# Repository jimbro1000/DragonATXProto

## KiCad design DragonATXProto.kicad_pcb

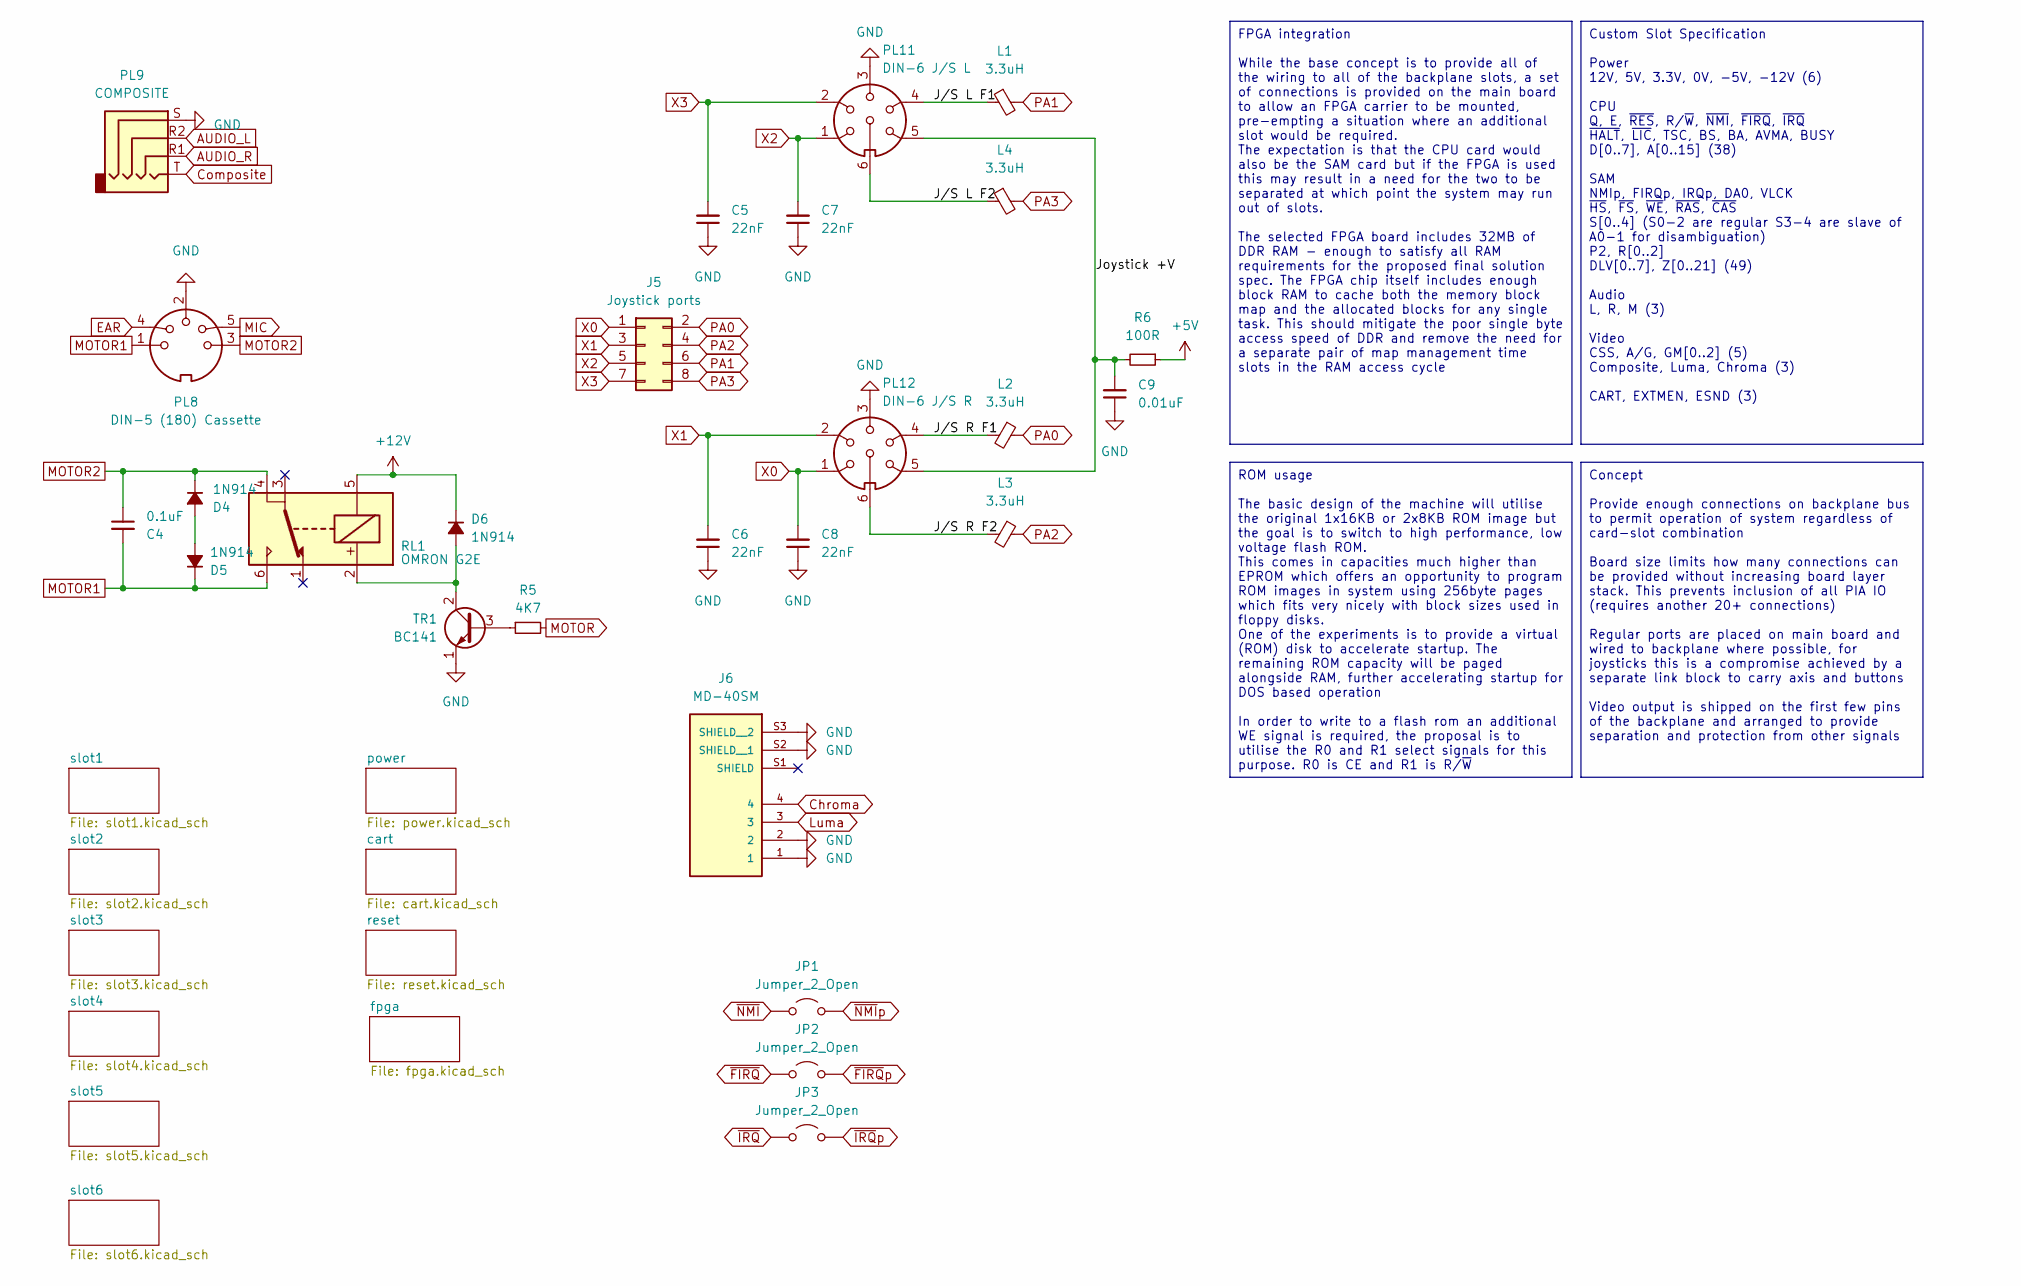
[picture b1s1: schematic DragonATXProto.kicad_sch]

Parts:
C4: 0.1uF; C_Disc_D4.3mm_W1.9mm_P5.00mm; DigiKey BC1101CT-ND
C5, C6, C7, C8: 22nF; C_Disc_D5.0mm_W2.5mm_P5.00mm; DigiKey BC2677CT-ND
C9: 0.01uF; C_Disc_D4.3mm_W1.9mm_P5.00mm; DigiKey BC2662CT-ND
D4, D5, D6: 1N914; D_DO-35_SOD27_P12.70mm_Horizontal; DigiKey 1N914FS-ND
J5: Joystick ports; PinHeader_2x04_P2.54mm_Vertical
J6: MD-40SM; CUI_MD-40SM; PARTREV 02/18/2022
JP1, JP2, JP3: Jumper_2_Open; SolderJumper-2_P1.3mm_Open_RoundedPad1.0x1.5mm
L1, L2, L3, L4: 3.3uH; L_Axial_L7.0mm_D3.3mm_P12.70mm_Horizontal_Fastron_MICC; DigiKey 495-5561-1-ND
PL8: DIN-5 (180) Cassette; DIN-5_DELTRON_671-0501_45deg_Horizontal
PL9: COMPOSITE; Jack_3.5mm_PJ320E_Horizontal
PL11: DIN-6 J/S L; DIN-6_DELTRON_671-0601_Horizontal
PL12: DIN-6 J/S R; DIN-6_DELTRON_671-0601_Horizontal
R5: 4K7; R_Axial_DIN0204_L3.6mm_D1.6mm_P2.54mm_Vertical; DigiKey CF14JT4K70CT-ND
R6: 100R; R_Axial_DIN0204_L3.6mm_D1.6mm_P2.54mm_Vertical; DigiKey CF14JT100RCT-ND
RL1: OMRON G2E; OMRON_G2E
TR1: BC141; TO-92

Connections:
+5V: R6.1; also elsewhere on the board
+12V: D6.1 (K), RL1.5; also elsewhere on the board
/Joystick +V: C9.2, PL11.5, PL12.5, R6.2
/J/S L F1: L1.1, PL11.4
/J/S L F2: L4.1, PL11.6
/J/S R F1: L2.2, PL12.4
/J/S R F2: L3.2, PL12.6
AUDIO_L: PL9.R2; also elsewhere on the board
AUDIO_R: PL9.R1; also elsewhere on the board
Chroma: J6.4; also elsewhere on the board
Composite: PL9.T; also elsewhere on the board
EAR: PL8.4; also elsewhere on the board
GND: C5.1, C6.1, C7.1, C8.1, C9.1, J6.1, J6.2, J6.S2 (SHIELD__1), J6.S3 (SHIELD__2), PL8.2, PL9.S, PL11.3, PL12.3, TR1.1 (E); also elsewhere on the board
Luma: J6.3; also elsewhere on the board
MIC: PL8.5; also elsewhere on the board
MOTOR: R5.2; also elsewhere on the board
MOTOR1: C4.2, D5.1 (K), PL8.1, RL1.6
MOTOR2: C4.1, D4.1 (K), PL8.3, RL1.4
unnamed: D4.2 (A), D5.2 (A)
unnamed: D6.2 (A), RL1.2, TR1.2 (C)
unnamed: R5.1, TR1.3 (B)
PA0: J5.2, L2.1
PA1: J5.6, L1.2
PA2: J5.4, L3.1
PA3: J5.8, L4.2
X0: C8.2, J5.1, PL12.1
X1: C6.2, J5.3, PL12.2
X2: C7.2, J5.5, PL11.1
X3: C5.2, J5.7, PL11.2
~FIRQ: JP2.1 (A); also elsewhere on the board
~FIRQp: JP2.2 (B); also elsewhere on the board
~IRQ: JP3.1 (A); also elsewhere on the board
~IRQp: JP3.2 (B); also elsewhere on the board
~NMI: JP1.1 (A); also elsewhere on the board
~NMIp: JP1.2 (B); also elsewhere on the board

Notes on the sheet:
ROM usage The basic design of the machine will utilise the original 1x16KB or 2x8KB ROM image but the goal is to switch to high performance, low voltage flash ROM. This comes in capacities much higher than EPROM which offers an opportunity to program ROM images in system using 256byte pages which f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
FPGA integration While the base concept is to provide all of the wiring to all of the backplane slots, a set of connections is provided on the main board to allow an FPGA carrier to be mounted, pre-empting a situation where an additional slot would be required. The expectation is that the CPU card 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
Custom Slot Specification Power 12V, 5V, 3.3V, 0V, -5V, -12V (6) CPU Q, E, ~{RES}, R/~{W}, ~{NMI}, ~{FIRQ}, ~{IRQ} ~{HALT}, ~{LIC}, TSC, BS, BA, AVMA, BUSY D[0..7], A[0..15] (38) SAM NMIp, FIRQp, IRQp, DA0, VLCK ~{HS}, ~{FS}, ~{WE}, ~{RAS}, ~{CAS} S[0..4] (S0-2 are regular S3-4 are slave of A0-1 fo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
Concept Provide enough connections on backplane bus to permit operation of system regardless of card-slot combination Board size limits how many connections can be provided without increasing board layer stack. This prevents inclusion of all PIA IO (requires another 20+ connections) Regular ports a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

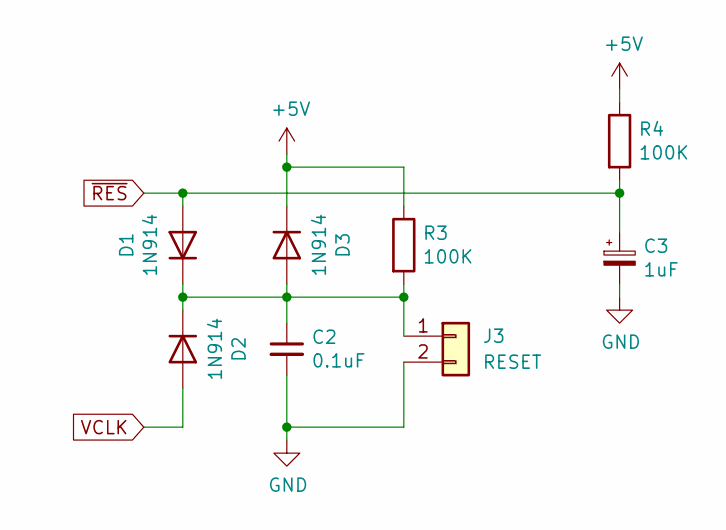
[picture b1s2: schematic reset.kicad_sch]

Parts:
C2: 0.1uF; C_Disc_D4.3mm_W1.9mm_P5.00mm; DigiKey 399-C0805C104K4RAC7800CT-ND
C3: 1uF; CP_Radial_D8.0mm_P5.00mm; DigiKey 732-8541-1-ND
D1, D2, D3: 1N914; D_DO-34_SOD68_P7.62mm_Horizontal; DigiKey 1N914FS-ND
J3: RESET; PinHeader_1x02_P2.54mm_Vertical
R3, R4: 100K; R_Axial_DIN0204_L3.6mm_D1.6mm_P2.54mm_Vertical; DigiKey 738-RNCF0805DTE100KCT-ND

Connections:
+5V: D3.1 (K), R3.1, R4.1; also elsewhere on the board
GND: C2.2, C3.2, J3.2; also elsewhere on the board
unnamed: C2.1, D1.1 (K), D2.1 (K), D3.2 (A), J3.1, R3.2
VCLK: D2.2 (A); also elsewhere on the board
~RES: C3.1, D1.2 (A), R4.2

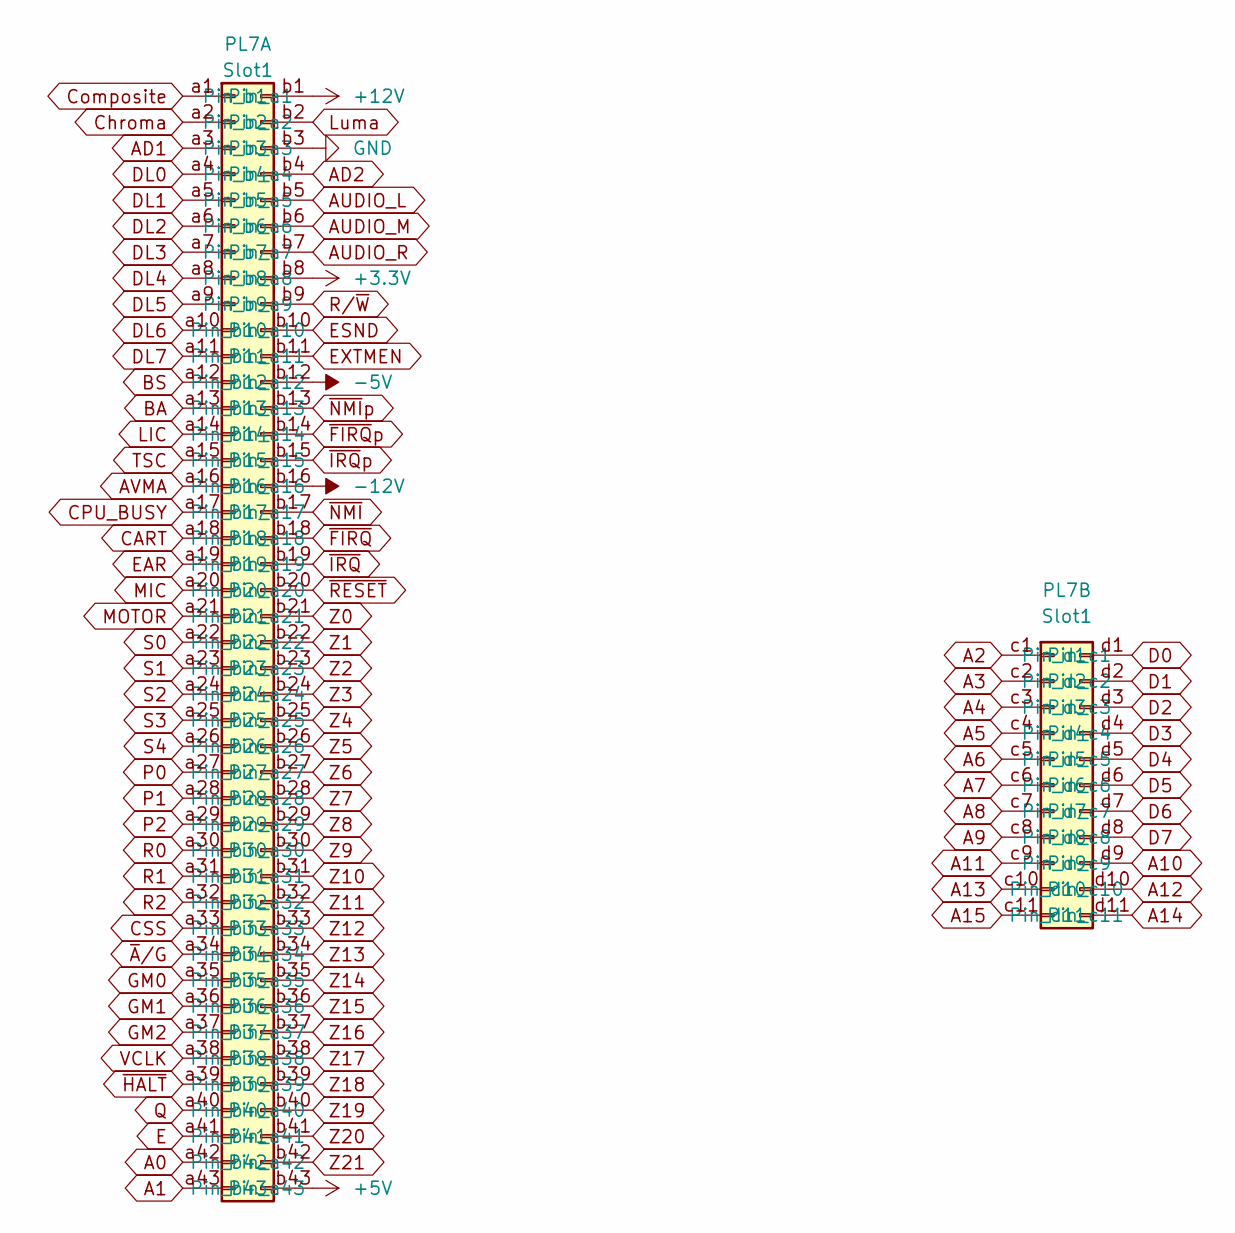
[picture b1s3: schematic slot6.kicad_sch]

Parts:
PL7: Slot1; Card_Edge

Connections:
+3.3V: PL7.b8; also elsewhere on the board
+5V: PL7.b43; also elsewhere on the board
+12V: PL7.b1; also elsewhere on the board
-5V: PL7.b12; also elsewhere on the board
-12V: PL7.b16; also elsewhere on the board
A0: PL7.a42; also elsewhere on the board
A1: PL7.a43; also elsewhere on the board
A2: PL7.c1; also elsewhere on the board
A3: PL7.c2; also elsewhere on the board
A4: PL7.c3; also elsewhere on the board
A5: PL7.c4; also elsewhere on the board
A6: PL7.c5; also elsewhere on the board
A7: PL7.c6; also elsewhere on the board
A8: PL7.c7; also elsewhere on the board
A9: PL7.c8; also elsewhere on the board
A10: PL7.d9; also elsewhere on the board
A11: PL7.c9; also elsewhere on the board
A12: PL7.d10; also elsewhere on the board
A13: PL7.c10; also elsewhere on the board
A14: PL7.d11; also elsewhere on the board
A15: PL7.c11; also elsewhere on the board
AD1: PL7.a3; also elsewhere on the board
AD2: PL7.b4; also elsewhere on the board
AUDIO_L: PL7.b5; also elsewhere on the board
AUDIO_M: PL7.b6; also elsewhere on the board
AUDIO_R: PL7.b7; also elsewhere on the board
AVMA: PL7.a16; also elsewhere on the board
BA: PL7.a13; also elsewhere on the board
BS: PL7.a12; also elsewhere on the board
CART: PL7.a18; also elsewhere on the board
CPU_BUSY: PL7.a17; also elsewhere on the board
CSS: PL7.a33; also elsewhere on the board
Chroma: PL7.a2; also elsewhere on the board
Composite: PL7.a1; also elsewhere on the board
D0: PL7.d1; also elsewhere on the board
D1: PL7.d2; also elsewhere on the board
D2: PL7.d3; also elsewhere on the board
D3: PL7.d4; also elsewhere on the board
D4: PL7.d5; also elsewhere on the board
D5: PL7.d6; also elsewhere on the board
D6: PL7.d7; also elsewhere on the board
D7: PL7.d8; also elsewhere on the board
DL0: PL7.a4; also elsewhere on the board
DL1: PL7.a5; also elsewhere on the board
DL2: PL7.a6; also elsewhere on the board
DL3: PL7.a7; also elsewhere on the board
DL4: PL7.a8; also elsewhere on the board
DL5: PL7.a9; also elsewhere on the board
DL6: PL7.a10; also elsewhere on the board
DL7: PL7.a11; also elsewhere on the board
E: PL7.a41; also elsewhere on the board
EAR: PL7.a19; also elsewhere on the board
ESND: PL7.b10; also elsewhere on the board
EXTMEN: PL7.b11; also elsewhere on the board
GM0: PL7.a35; also elsewhere on the board
GM1: PL7.a36; also elsewhere on the board
GM2: PL7.a37; also elsewhere on the board
GND: PL7.b3; also elsewhere on the board
LIC: PL7.a14; also elsewhere on the board
Luma: PL7.b2; also elsewhere on the board
MIC: PL7.a20; also elsewhere on the board
MOTOR: PL7.a21; also elsewhere on the board
P0: PL7.a27; also elsewhere on the board
P1: PL7.a28; also elsewhere on the board
P2: PL7.a29; also elsewhere on the board
Q: PL7.a40; also elsewhere on the board
R0: PL7.a30; also elsewhere on the board
R1: PL7.a31; also elsewhere on the board
R2: PL7.a32; also elsewhere on the board
R/~W: PL7.b9; also elsewhere on the board
S0: PL7.a22; also elsewhere on the board
S1: PL7.a23; also elsewhere on the board
S2: PL7.a24; also elsewhere on the board
S3: PL7.a25; also elsewhere on the board
S4: PL7.a26; also elsewhere on the board
TSC: PL7.a15; also elsewhere on the board
VCLK: PL7.a38; also elsewhere on the board
Z0: PL7.b21; also elsewhere on the board
Z1: PL7.b22; also elsewhere on the board
Z2: PL7.b23; also elsewhere on the board
Z3: PL7.b24; also elsewhere on the board
Z4: PL7.b25; also elsewhere on the board
Z5: PL7.b26; also elsewhere on the board
Z6: PL7.b27; also elsewhere on the board
Z7: PL7.b28; also elsewhere on the board
Z8: PL7.b29; also elsewhere on the board
Z9: PL7.b30; also elsewhere on the board
Z10: PL7.b31; also elsewhere on the board
Z11: PL7.b32; also elsewhere on the board
Z12: PL7.b33; also elsewhere on the board
Z13: PL7.b34; also elsewhere on the board
Z14: PL7.b35; also elsewhere on the board
Z15: PL7.b36; also elsewhere on the board
Z16: PL7.b37; also elsewhere on the board
Z17: PL7.b38; also elsewhere on the board
Z18: PL7.b39; also elsewhere on the board
Z19: PL7.b40; also elsewhere on the board
Z20: PL7.b41; also elsewhere on the board
Z21: PL7.b42; also elsewhere on the board
~A/G: PL7.a34; also elsewhere on the board
~FIRQ: PL7.b18; also elsewhere on the board
~FIRQp: PL7.b14; also elsewhere on the board
~HALT: PL7.a39; also elsewhere on the board
~IRQ: PL7.b19; also elsewhere on the board
~IRQp: PL7.b15; also elsewhere on the board
~NMI: PL7.b17; also elsewhere on the board
~NMIp: PL7.b13; also elsewhere on the board
~RESET: PL7.b20; also elsewhere on the board

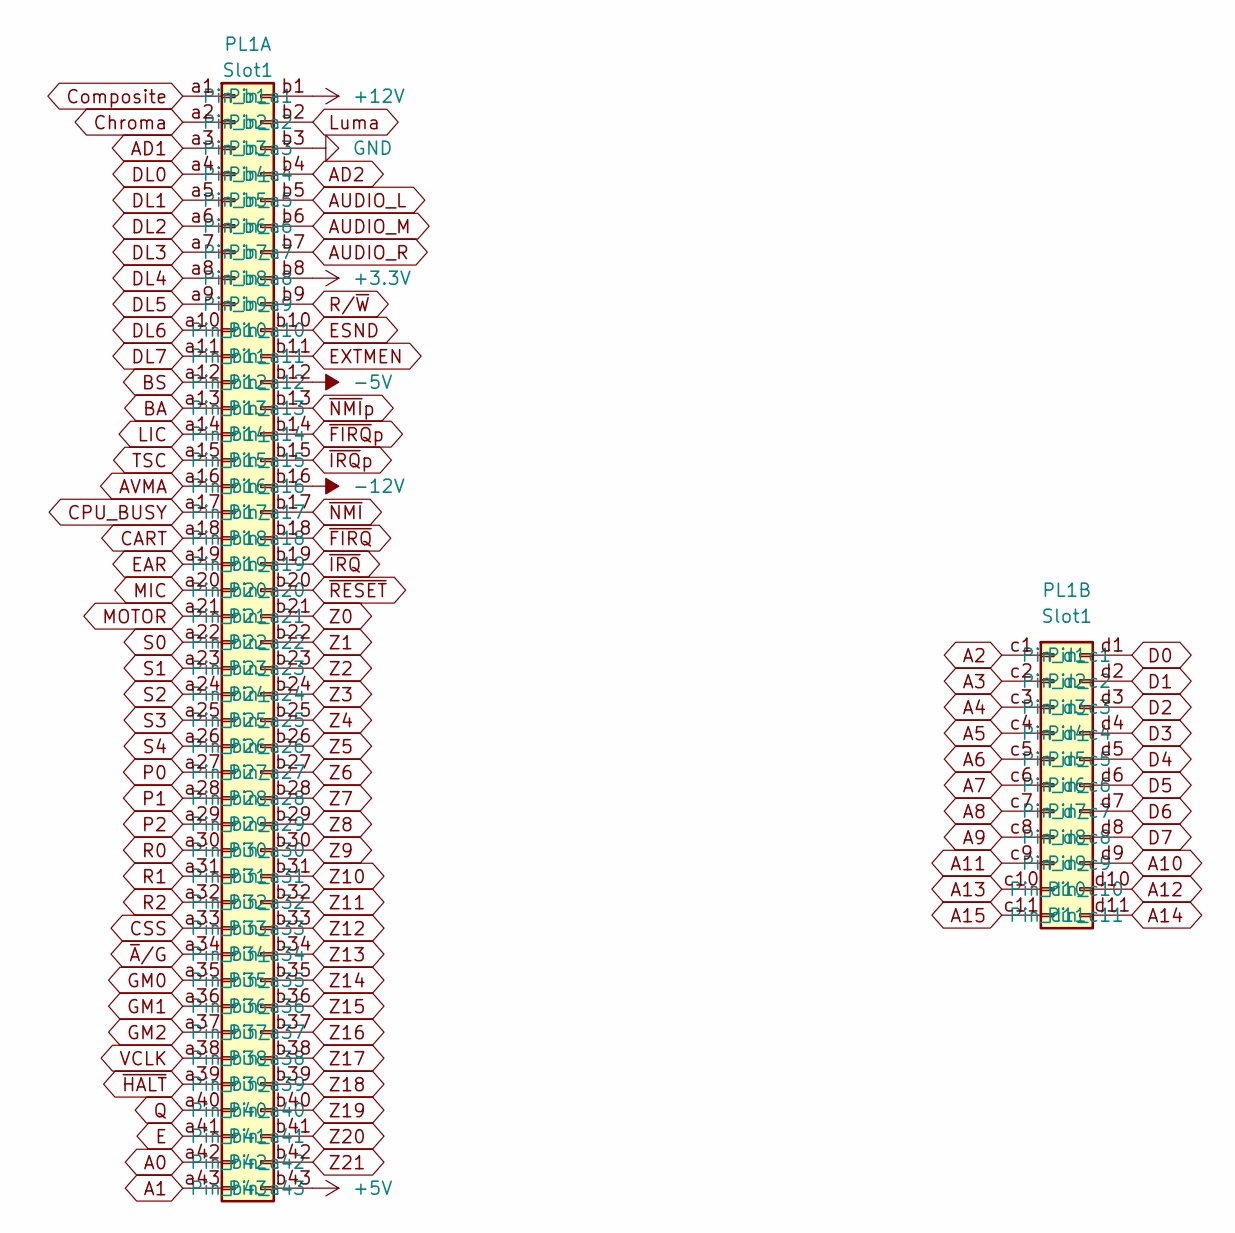
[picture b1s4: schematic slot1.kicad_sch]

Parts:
PL1: Slot1; Card_Edge

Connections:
+3.3V: PL1.b8; also elsewhere on the board
+5V: PL1.b43; also elsewhere on the board
+12V: PL1.b1; also elsewhere on the board
-5V: PL1.b12; also elsewhere on the board
-12V: PL1.b16; also elsewhere on the board
A0: PL1.a42; also elsewhere on the board
A1: PL1.a43; also elsewhere on the board
A2: PL1.c1; also elsewhere on the board
A3: PL1.c2; also elsewhere on the board
A4: PL1.c3; also elsewhere on the board
A5: PL1.c4; also elsewhere on the board
A6: PL1.c5; also elsewhere on the board
A7: PL1.c6; also elsewhere on the board
A8: PL1.c7; also elsewhere on the board
A9: PL1.c8; also elsewhere on the board
A10: PL1.d9; also elsewhere on the board
A11: PL1.c9; also elsewhere on the board
A12: PL1.d10; also elsewhere on the board
A13: PL1.c10; also elsewhere on the board
A14: PL1.d11; also elsewhere on the board
A15: PL1.c11; also elsewhere on the board
AD1: PL1.a3; also elsewhere on the board
AD2: PL1.b4; also elsewhere on the board
AUDIO_L: PL1.b5; also elsewhere on the board
AUDIO_M: PL1.b6; also elsewhere on the board
AUDIO_R: PL1.b7; also elsewhere on the board
AVMA: PL1.a16; also elsewhere on the board
BA: PL1.a13; also elsewhere on the board
BS: PL1.a12; also elsewhere on the board
CART: PL1.a18; also elsewhere on the board
CPU_BUSY: PL1.a17; also elsewhere on the board
CSS: PL1.a33; also elsewhere on the board
Chroma: PL1.a2; also elsewhere on the board
Composite: PL1.a1; also elsewhere on the board
D0: PL1.d1; also elsewhere on the board
D1: PL1.d2; also elsewhere on the board
D2: PL1.d3; also elsewhere on the board
D3: PL1.d4; also elsewhere on the board
D4: PL1.d5; also elsewhere on the board
D5: PL1.d6; also elsewhere on the board
D6: PL1.d7; also elsewhere on the board
D7: PL1.d8; also elsewhere on the board
DL0: PL1.a4; also elsewhere on the board
DL1: PL1.a5; also elsewhere on the board
DL2: PL1.a6; also elsewhere on the board
DL3: PL1.a7; also elsewhere on the board
DL4: PL1.a8; also elsewhere on the board
DL5: PL1.a9; also elsewhere on the board
DL6: PL1.a10; also elsewhere on the board
DL7: PL1.a11; also elsewhere on the board
E: PL1.a41; also elsewhere on the board
EAR: PL1.a19; also elsewhere on the board
ESND: PL1.b10; also elsewhere on the board
EXTMEN: PL1.b11; also elsewhere on the board
GM0: PL1.a35; also elsewhere on the board
GM1: PL1.a36; also elsewhere on the board
GM2: PL1.a37; also elsewhere on the board
GND: PL1.b3; also elsewhere on the board
LIC: PL1.a14; also elsewhere on the board
Luma: PL1.b2; also elsewhere on the board
MIC: PL1.a20; also elsewhere on the board
MOTOR: PL1.a21; also elsewhere on the board
P0: PL1.a27; also elsewhere on the board
P1: PL1.a28; also elsewhere on the board
P2: PL1.a29; also elsewhere on the board
Q: PL1.a40; also elsewhere on the board
R0: PL1.a30; also elsewhere on the board
R1: PL1.a31; also elsewhere on the board
R2: PL1.a32; also elsewhere on the board
R/~W: PL1.b9; also elsewhere on the board
S0: PL1.a22; also elsewhere on the board
S1: PL1.a23; also elsewhere on the board
S2: PL1.a24; also elsewhere on the board
S3: PL1.a25; also elsewhere on the board
S4: PL1.a26; also elsewhere on the board
TSC: PL1.a15; also elsewhere on the board
VCLK: PL1.a38; also elsewhere on the board
Z0: PL1.b21; also elsewhere on the board
Z1: PL1.b22; also elsewhere on the board
Z2: PL1.b23; also elsewhere on the board
Z3: PL1.b24; also elsewhere on the board
Z4: PL1.b25; also elsewhere on the board
Z5: PL1.b26; also elsewhere on the board
Z6: PL1.b27; also elsewhere on the board
Z7: PL1.b28; also elsewhere on the board
Z8: PL1.b29; also elsewhere on the board
Z9: PL1.b30; also elsewhere on the board
Z10: PL1.b31; also elsewhere on the board
Z11: PL1.b32; also elsewhere on the board
Z12: PL1.b33; also elsewhere on the board
Z13: PL1.b34; also elsewhere on the board
Z14: PL1.b35; also elsewhere on the board
Z15: PL1.b36; also elsewhere on the board
Z16: PL1.b37; also elsewhere on the board
Z17: PL1.b38; also elsewhere on the board
Z18: PL1.b39; also elsewhere on the board
Z19: PL1.b40; also elsewhere on the board
Z20: PL1.b41; also elsewhere on the board
Z21: PL1.b42; also elsewhere on the board
~A/G: PL1.a34; also elsewhere on the board
~FIRQ: PL1.b18; also elsewhere on the board
~FIRQp: PL1.b14; also elsewhere on the board
~HALT: PL1.a39; also elsewhere on the board
~IRQ: PL1.b19; also elsewhere on the board
~IRQp: PL1.b15; also elsewhere on the board
~NMI: PL1.b17; also elsewhere on the board
~NMIp: PL1.b13; also elsewhere on the board
~RESET: PL1.b20; also elsewhere on the board

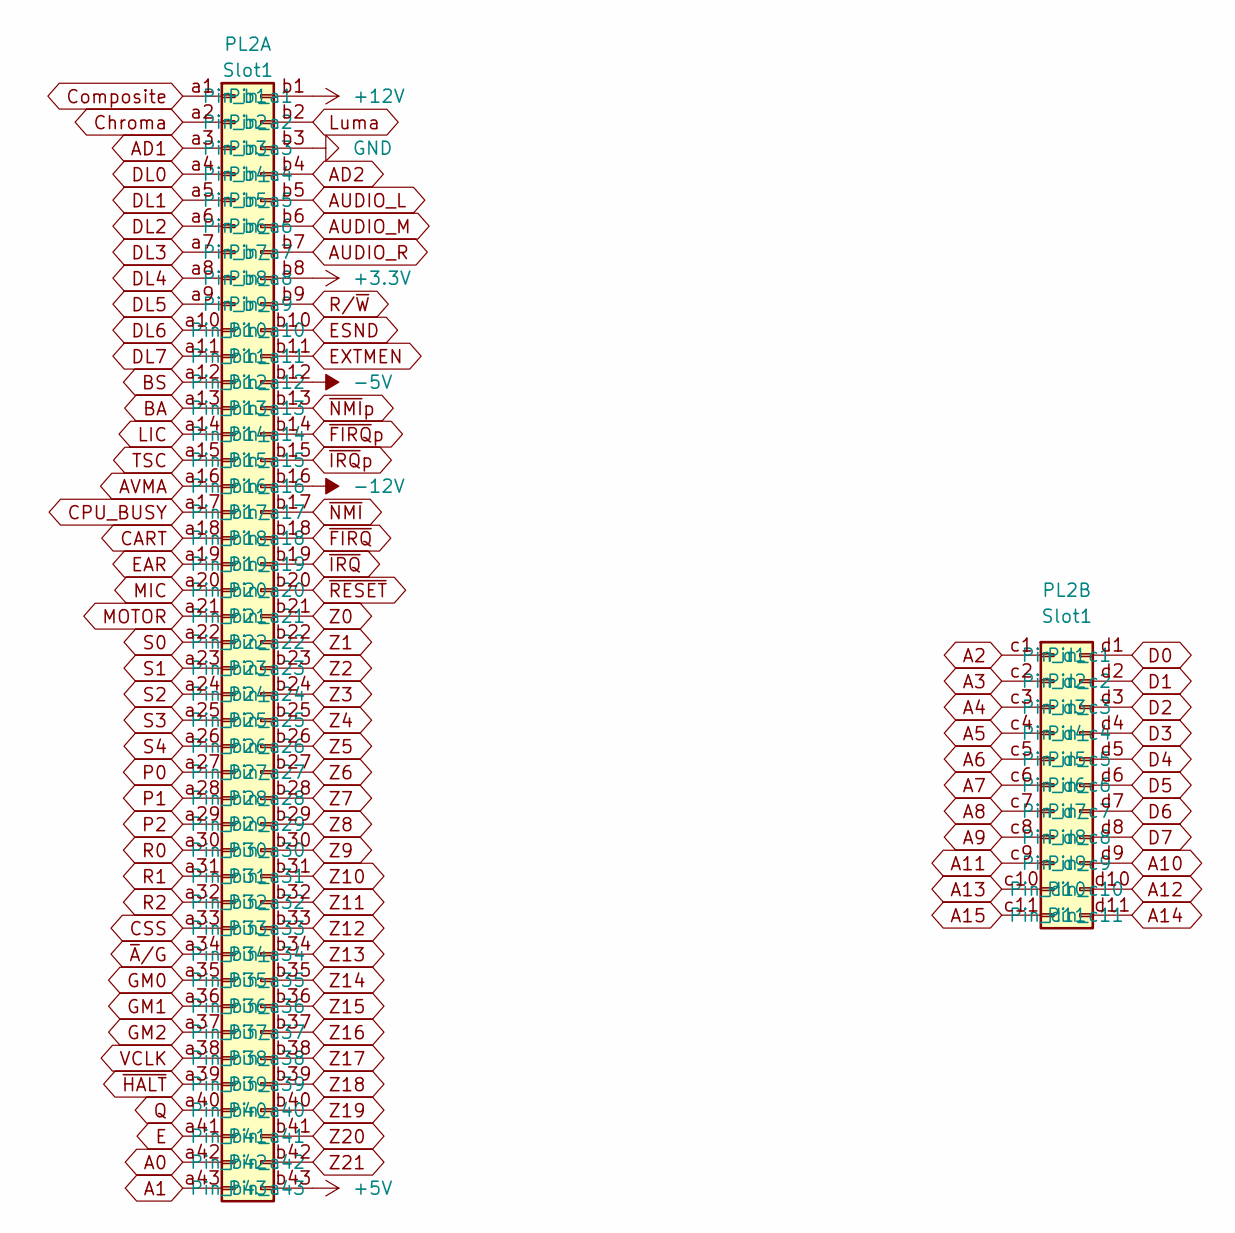
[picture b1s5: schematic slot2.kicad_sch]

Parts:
PL2: Slot1; Card_Edge

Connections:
+3.3V: PL2.b8; also elsewhere on the board
+5V: PL2.b43; also elsewhere on the board
+12V: PL2.b1; also elsewhere on the board
-5V: PL2.b12; also elsewhere on the board
-12V: PL2.b16; also elsewhere on the board
A0: PL2.a42; also elsewhere on the board
A1: PL2.a43; also elsewhere on the board
A2: PL2.c1; also elsewhere on the board
A3: PL2.c2; also elsewhere on the board
A4: PL2.c3; also elsewhere on the board
A5: PL2.c4; also elsewhere on the board
A6: PL2.c5; also elsewhere on the board
A7: PL2.c6; also elsewhere on the board
A8: PL2.c7; also elsewhere on the board
A9: PL2.c8; also elsewhere on the board
A10: PL2.d9; also elsewhere on the board
A11: PL2.c9; also elsewhere on the board
A12: PL2.d10; also elsewhere on the board
A13: PL2.c10; also elsewhere on the board
A14: PL2.d11; also elsewhere on the board
A15: PL2.c11; also elsewhere on the board
AD1: PL2.a3; also elsewhere on the board
AD2: PL2.b4; also elsewhere on the board
AUDIO_L: PL2.b5; also elsewhere on the board
AUDIO_M: PL2.b6; also elsewhere on the board
AUDIO_R: PL2.b7; also elsewhere on the board
AVMA: PL2.a16; also elsewhere on the board
BA: PL2.a13; also elsewhere on the board
BS: PL2.a12; also elsewhere on the board
CART: PL2.a18; also elsewhere on the board
CPU_BUSY: PL2.a17; also elsewhere on the board
CSS: PL2.a33; also elsewhere on the board
Chroma: PL2.a2; also elsewhere on the board
Composite: PL2.a1; also elsewhere on the board
D0: PL2.d1; also elsewhere on the board
D1: PL2.d2; also elsewhere on the board
D2: PL2.d3; also elsewhere on the board
D3: PL2.d4; also elsewhere on the board
D4: PL2.d5; also elsewhere on the board
D5: PL2.d6; also elsewhere on the board
D6: PL2.d7; also elsewhere on the board
D7: PL2.d8; also elsewhere on the board
DL0: PL2.a4; also elsewhere on the board
DL1: PL2.a5; also elsewhere on the board
DL2: PL2.a6; also elsewhere on the board
DL3: PL2.a7; also elsewhere on the board
DL4: PL2.a8; also elsewhere on the board
DL5: PL2.a9; also elsewhere on the board
DL6: PL2.a10; also elsewhere on the board
DL7: PL2.a11; also elsewhere on the board
E: PL2.a41; also elsewhere on the board
EAR: PL2.a19; also elsewhere on the board
ESND: PL2.b10; also elsewhere on the board
EXTMEN: PL2.b11; also elsewhere on the board
GM0: PL2.a35; also elsewhere on the board
GM1: PL2.a36; also elsewhere on the board
GM2: PL2.a37; also elsewhere on the board
GND: PL2.b3; also elsewhere on the board
LIC: PL2.a14; also elsewhere on the board
Luma: PL2.b2; also elsewhere on the board
MIC: PL2.a20; also elsewhere on the board
MOTOR: PL2.a21; also elsewhere on the board
P0: PL2.a27; also elsewhere on the board
P1: PL2.a28; also elsewhere on the board
P2: PL2.a29; also elsewhere on the board
Q: PL2.a40; also elsewhere on the board
R0: PL2.a30; also elsewhere on the board
R1: PL2.a31; also elsewhere on the board
R2: PL2.a32; also elsewhere on the board
R/~W: PL2.b9; also elsewhere on the board
S0: PL2.a22; also elsewhere on the board
S1: PL2.a23; also elsewhere on the board
S2: PL2.a24; also elsewhere on the board
S3: PL2.a25; also elsewhere on the board
S4: PL2.a26; also elsewhere on the board
TSC: PL2.a15; also elsewhere on the board
VCLK: PL2.a38; also elsewhere on the board
Z0: PL2.b21; also elsewhere on the board
Z1: PL2.b22; also elsewhere on the board
Z2: PL2.b23; also elsewhere on the board
Z3: PL2.b24; also elsewhere on the board
Z4: PL2.b25; also elsewhere on the board
Z5: PL2.b26; also elsewhere on the board
Z6: PL2.b27; also elsewhere on the board
Z7: PL2.b28; also elsewhere on the board
Z8: PL2.b29; also elsewhere on the board
Z9: PL2.b30; also elsewhere on the board
Z10: PL2.b31; also elsewhere on the board
Z11: PL2.b32; also elsewhere on the board
Z12: PL2.b33; also elsewhere on the board
Z13: PL2.b34; also elsewhere on the board
Z14: PL2.b35; also elsewhere on the board
Z15: PL2.b36; also elsewhere on the board
Z16: PL2.b37; also elsewhere on the board
Z17: PL2.b38; also elsewhere on the board
Z18: PL2.b39; also elsewhere on the board
Z19: PL2.b40; also elsewhere on the board
Z20: PL2.b41; also elsewhere on the board
Z21: PL2.b42; also elsewhere on the board
~A/G: PL2.a34; also elsewhere on the board
~FIRQ: PL2.b18; also elsewhere on the board
~FIRQp: PL2.b14; also elsewhere on the board
~HALT: PL2.a39; also elsewhere on the board
~IRQ: PL2.b19; also elsewhere on the board
~IRQp: PL2.b15; also elsewhere on the board
~NMI: PL2.b17; also elsewhere on the board
~NMIp: PL2.b13; also elsewhere on the board
~RESET: PL2.b20; also elsewhere on the board
